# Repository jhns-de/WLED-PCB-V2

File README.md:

# WLED PCB V2

This is an ESP8266 based controller to drive addressable 12V [GS8208](www.normandled.com/upload/201805/GS8208%20LED%20Datasheet.pdf) LED Strips with the amazing [WLED](https://github.com/Aircoookie/WLED) firmware.

**This PCB was designed in [KiCad](https://www.kicad.org/).**

## Features

- Dimensions 95mm x 40mm
- Onboard LED for testing
- Fuse for overcurrent protection
- Reverse polarity protection for input and output
- [Recommended](https://kno.wled.ge/basics/compatible-hardware/#levelshifters) SN74AHCT125N Levelshifter
- Multiple decoupling capacitors
- IR receiver
- Relay for completely switching of the LED Stripe
- INA219 power sensor
- Multiple test points
- Onboard LED Stripe extension adapter

## Goal

This PCB was designed as an LED Stripe controller board for digital 12V GS8208 LED Strips built into a shelf. Therefore, it had to be easy to connect the LED Strips on either side of the board (depending if the board is mounted on the left or right side of the shelf). In addition, the LED Stripe hat to be easy extendable over the board, so the LED Stripe doesn't end before the shelf ends.

## More Information

Due to the backup line of the GS8208 LED design it is possible to completely remove the test led or the onboard led stripe extension adapter.

## Warning

In my first revision I connected the INA219 improperly. Therefore, I was unable to use it and never got to actually implementing the sensor into WLED. I updated the schematics and board to connect the INA219 sensor properly, but better check twice.

## WLED PCB V2

### Schematic

### PCB

#### Front

#### Back

## WLED PCB V2 LEDs

This is the onboard LED Stripe extension adapter, to extend the LED Stripe over the PCB board, so that the light ends at the end of the shelf. It contains 3 more GS8208 LEDs to extend the LED Stripe. By design it is possible to mount it in both directions, so it can be swapped if the controller is mounted on the other side of the shelf.

### Schematic

### PCB

The PCB is 14.25mm x 40.00mm.

#### Front

#### Back

## Additional Information

### Photos

### PcbDraw Command for PCB Images

[PcbDraw](https://github.com/yaqwsx/PcbDraw) is a tool for generating nice looking PCB images from KiCad files.

```
pcbdraw plot WLED_PCB_V2_LEDs.kicad_pcb PCB_Back.png --side back --style set-blue-cu --no-components
```

## License

This project is licensed under the GNU GPLv3.

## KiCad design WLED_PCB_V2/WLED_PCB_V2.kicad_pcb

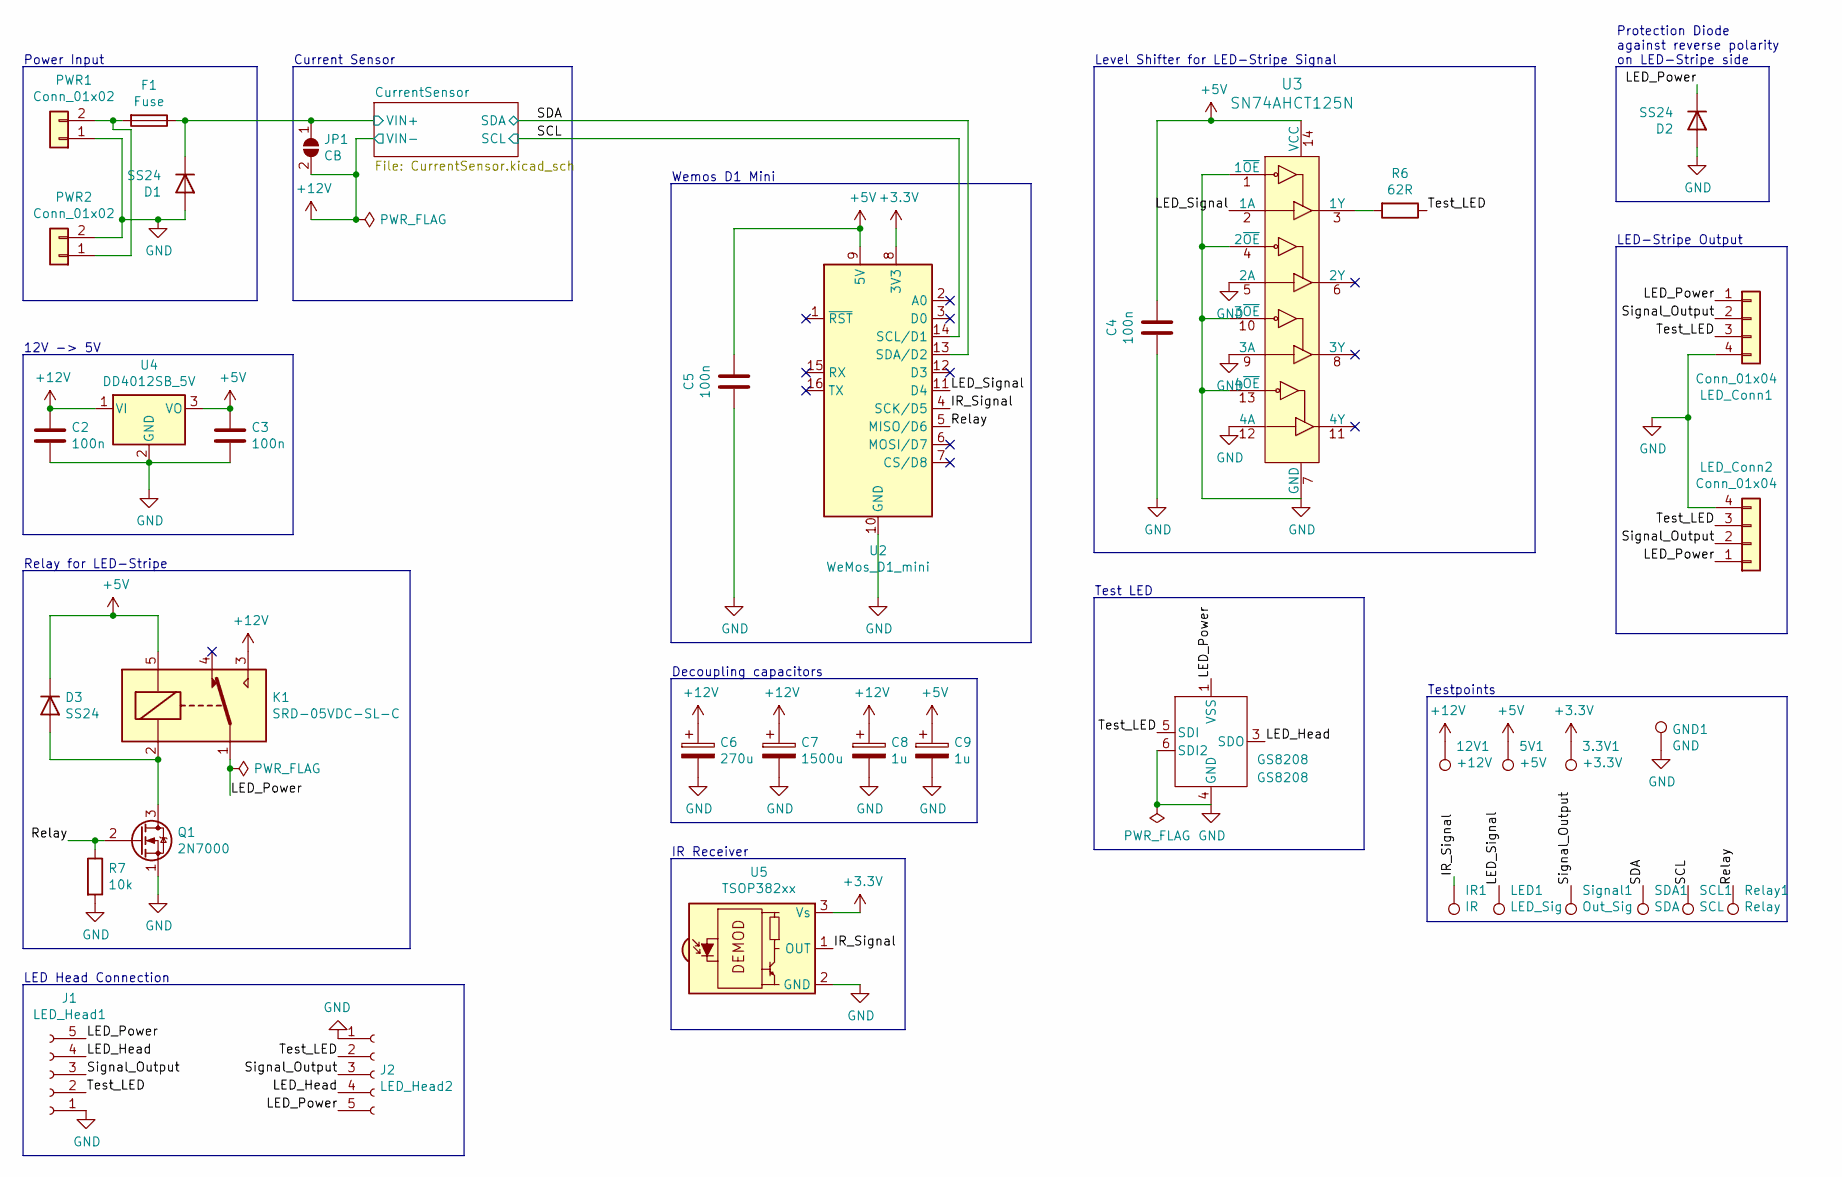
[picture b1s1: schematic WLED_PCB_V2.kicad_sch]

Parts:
3.3V1: +3.3V; TestPoint_Pad_1.5x1.5mm
5V1: +5V; TestPoint_Pad_1.5x1.5mm
12V1: +12V; TestPoint_Pad_1.5x1.5mm
C2, C3, C4, C5: 100n; C_0805_2012Metric_Pad1.15x1.40mm_HandSolder
C6: 270u; C_Radial_D8.0mm_H11.5mm_P3.50mm
C7: 1500u; C_Radial_D10.0mm_H20.0mm_P5.00mm
C8, C9: 1u; C_0805_2012Metric_Pad1.15x1.40mm_HandSolder
D1, D2, D3: SS24; D_SMB
F1: Fuse; Fuseholder_Cylinder-5x20mm_Schurter_0031_8201_Horizontal_Op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
GND1: GND; TestPoint_THTPad_D2.5mm_Drill1.2mm
GS8208: GS8208
IR1: IR; TestPoint_Pad_1.5x1.5mm
J1: LED_Head1; PinSocket_1x05_P2.54mm_Vertical
J2: LED_Head2; PinSocket_1x05_P2.54mm_Vertical
JP1: CB; SolderJumper-2_P1.3mm_Open_Pad1.0x1.5mm
K1: SRD-05VDC-SL-C; Relay_SPDT_SANYOU_SRD_Series_Form_C
LED1: LED_Sig; TestPoint_Pad_1.5x1.5mm
LED_Conn1, LED_Conn2: Conn_01x04; JST_XH_S4B-XH-A_1x04_P2.50mm_Horizontal
PWR1, PWR2: Conn_01x02; TerminalBlock_bornier-2_P5.08mm
Q1: 2N7000; TO-92_Inline
R6: 62R; R_0805_2012Metric_Pad1.15x1.40mm_HandSolder
R7: 10k; R_0805_2012Metric_Pad1.15x1.40mm_HandSolder
Relay1: Relay; TestPoint_Pad_1.5x1.5mm
SCL1: SCL; TestPoint_Pad_1.5x1.5mm
SDA1: SDA; TestPoint_Pad_1.5x1.5mm
Signal1: Out_Sig; TestPoint_Pad_1.5x1.5mm
U2: WeMos_D1_mini; WEMOS_D1_mini_light
U3: SN74AHCT125N; DIP-14_W3mm; MPN SN74AHCT125N; Digi-Key_PN 296-4655-5-ND
U4: DD4012SB_5V; DD4012S
U5: TSOP382xx; Vishay_MINICAST-3Pin

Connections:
+3V3: 3.3V1.1, U2.8 (3V3), U5.3 (Vs); also elsewhere on the board
+5V: 5V1.1, C3.1, C4.1, C5.1, C9.1, D3.1 (K), K1.5, U2.9 (5V), U3.14 (VCC), U4.3 (VO)
+12V: 12V1.1, C2.1, C6.1, C7.1, C8.1, JP1.2 (B), K1.3, U4.1 (VI); also elsewhere on the board
/CurrentSensor/VIN+: D1.1 (K), F1.1, JP1.1 (A); also elsewhere on the board
/IR_Signal: IR1.1, U2.4 (SCK/D5), U5.1 (OUT)
/LED_Head: GS8208.3 (SDO), J1.4, J2.4
/LED_Power: D2.1 (K), GS8208.1 (VSS), J1.5, J2.5, K1.1, LED_Conn1.1, LED_Conn2.1
/LED_Signal: LED1.1, U2.11 (D4), U3.2 (1A)
/Relay: Q1.2 (G), R7.1, Relay1.1, U2.5 (MISO/D6)
/SCL: SCL1.1, U2.14 (SCL/D1); also elsewhere on the board
/SDA: SDA1.1, U2.13 (SDA/D2); also elsewhere on the board
/Signal_Output: J1.3, J2.3, LED_Conn1.2, LED_Conn2.2, Signal1.1
/Test_LED: GS8208.5 (SDI), J1.2, J2.2, LED_Conn1.3, LED_Conn2.3, R6.1
GND: C2.2, C3.2, C4.2, C5.2, C6.2, C7.2, C8.2, C9.2, D1.2 (A), D2.2 (A), GND1.1, GS8208.4 (GND), GS8208.6 (SDI2), J1.1, J2.1, LED_Conn1.4, LED_Conn2.4, PWR1.1, PWR2.2, Q1.1 (S), R7.2, U2.10 (GND), U3.1 (1~OE), U3.4 (2~OE), U3.5 (2A), U3.7 (GND), U3.9 (3A), U3.10 (3~OE), U3.12 (4A), U3.13 (4~OE), U4.2 (GND), U5.2 (GND); also elsewhere on the board
unnamed: D3.2 (A), K1.2, Q1.3 (D)
unnamed: F1.2, PWR1.2, PWR2.1
unnamed: R6.2, U3.3 (1Y)

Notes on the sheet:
12V -> 5V
LED Head Connection
Relay for LED-Stripe
Current Sensor
Level Shifter for LED-Stripe Signal
Power Input
Test LED
IR Receiver
LED-Stripe Output
Testpoints
Protection Diode against reverse polarity on LED-Stripe side
Decoupling capacitors
Wemos D1 Mini

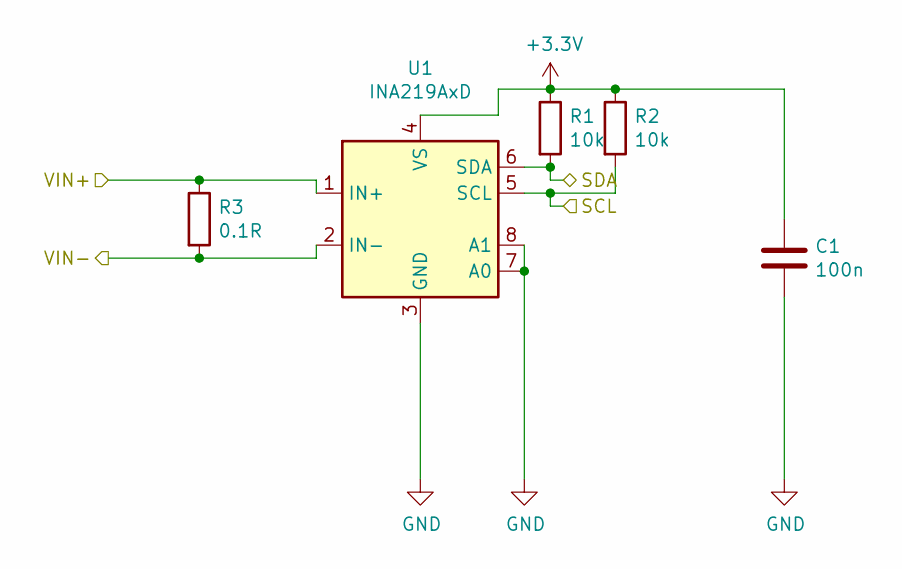
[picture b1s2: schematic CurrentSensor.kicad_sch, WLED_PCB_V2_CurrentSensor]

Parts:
C1: 100n; C_0805_2012Metric_Pad1.15x1.40mm_HandSolder
R1, R2: 10k; R_0805_2012Metric_Pad1.15x1.40mm_HandSolder
R3: 0.1R; R_2512_6332Metric_Pad1.52x3.35mm_HandSolder
U1: INA219AxD; SOT-23-8_Handsoldering

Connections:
+3V3: C1.1, R1.1, R2.1, U1.4 (VS); also elsewhere on the board
+12V: R3.2, U1.2 (IN-); also elsewhere on the board
/CurrentSensor/VIN+: R3.1, U1.1 (IN+); also elsewhere on the board
/SCL: R2.2, U1.5 (SCL); also elsewhere on the board
/SDA: R1.2, U1.6 (SDA); also elsewhere on the board
GND: C1.2, U1.3 (GND), U1.7 (A0), U1.8 (A1); also elsewhere on the board

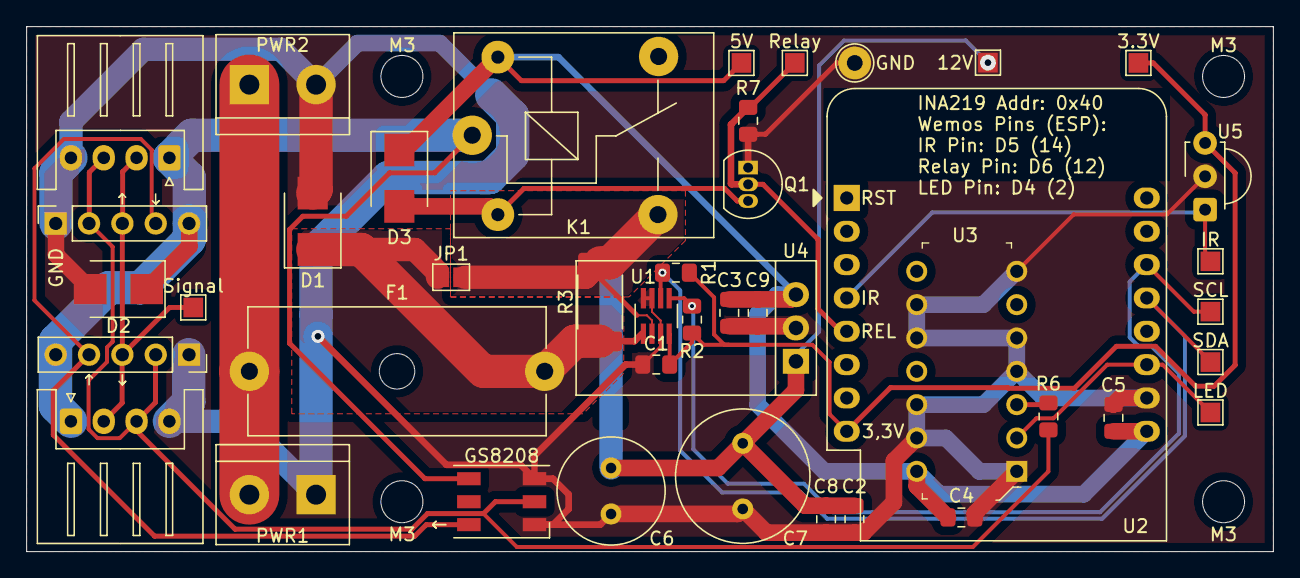
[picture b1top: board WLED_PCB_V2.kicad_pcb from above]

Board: 2 copper layers, 95.0 x 40.0 mm, 43 parts (0 on the bottom side), 17 nets.

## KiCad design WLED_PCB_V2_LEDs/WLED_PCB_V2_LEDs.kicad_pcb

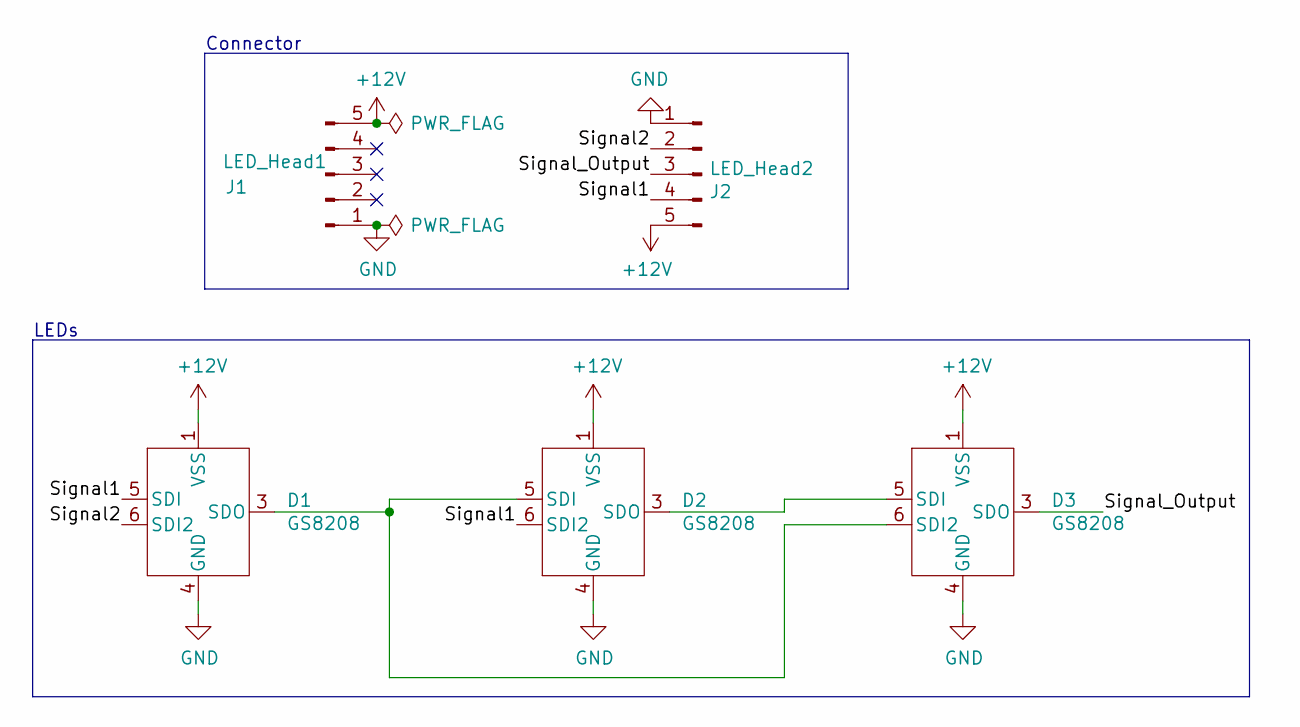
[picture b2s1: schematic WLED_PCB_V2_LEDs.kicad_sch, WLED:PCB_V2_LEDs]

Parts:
D1, D2, D3: GS8208
J1: LED_Head1; PinHeader_1x05_P2.54mm_Vertical
J2: LED_Head2; PinHeader_1x05_P2.54mm_Vertical

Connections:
+12V: D1.1 (VSS), D2.1 (VSS), D3.1 (VSS), J1.5, J2.5
/Signal1: D1.5 (SDI), D2.6 (SDI2), J2.4
/Signal2: D1.6 (SDI2), J2.2
/Signal_Output: D3.3 (SDO), J2.3
GND: D1.4 (GND), D2.4 (GND), D3.4 (GND), J1.1, J2.1
unnamed: D1.3 (SDO), D2.5 (SDI), D3.6 (SDI2)
unnamed: D2.3 (SDO), D3.5 (SDI)

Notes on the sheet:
Connector
LEDs

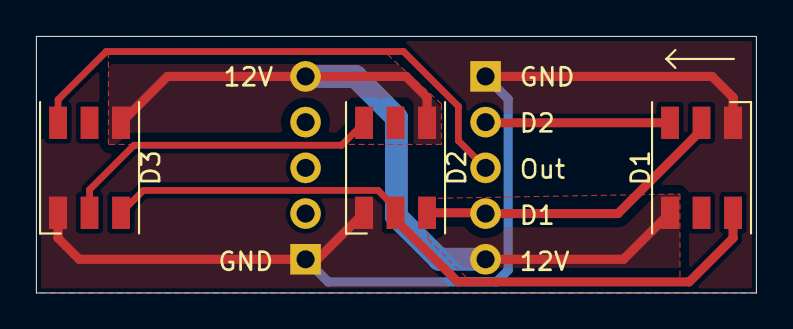
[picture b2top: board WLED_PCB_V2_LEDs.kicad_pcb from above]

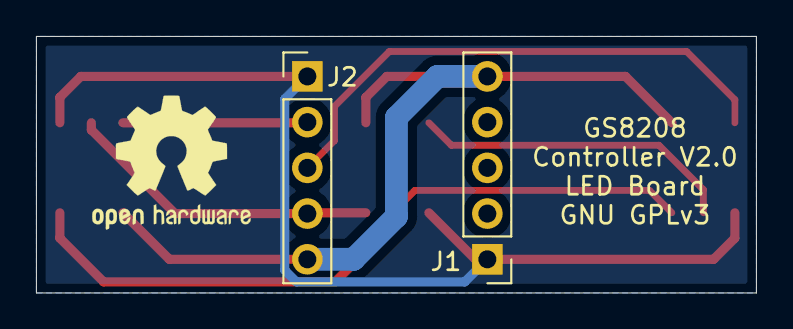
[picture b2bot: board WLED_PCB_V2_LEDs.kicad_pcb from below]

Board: 2 copper layers, 40.0 x 14.2 mm, 5 parts (2 on the bottom side), 7 nets.

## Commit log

2023-03-30 added license
2023-03-30 added custom symbols and PCBs
2023-03-30 added README
2023-03-30 added white background to schematics
